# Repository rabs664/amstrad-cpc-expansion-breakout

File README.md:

# amstrad-cpc-expansion-breakout
Simple PCB with labels and header pins for the Amstrad CPC Expansion Bus, compatible with an MX4 connector.

Allows Amstrad CPC Expansion bus signals to be monitored using the labels without having to remember the pin position on the connector.

Source contains Eagle schematic, board and cam output (gerber) files.

Note there is no ESD protection and the headers connect directly to the expansion bus, so care should be taken at all times to prevent accidents.

see Wiki for more info.

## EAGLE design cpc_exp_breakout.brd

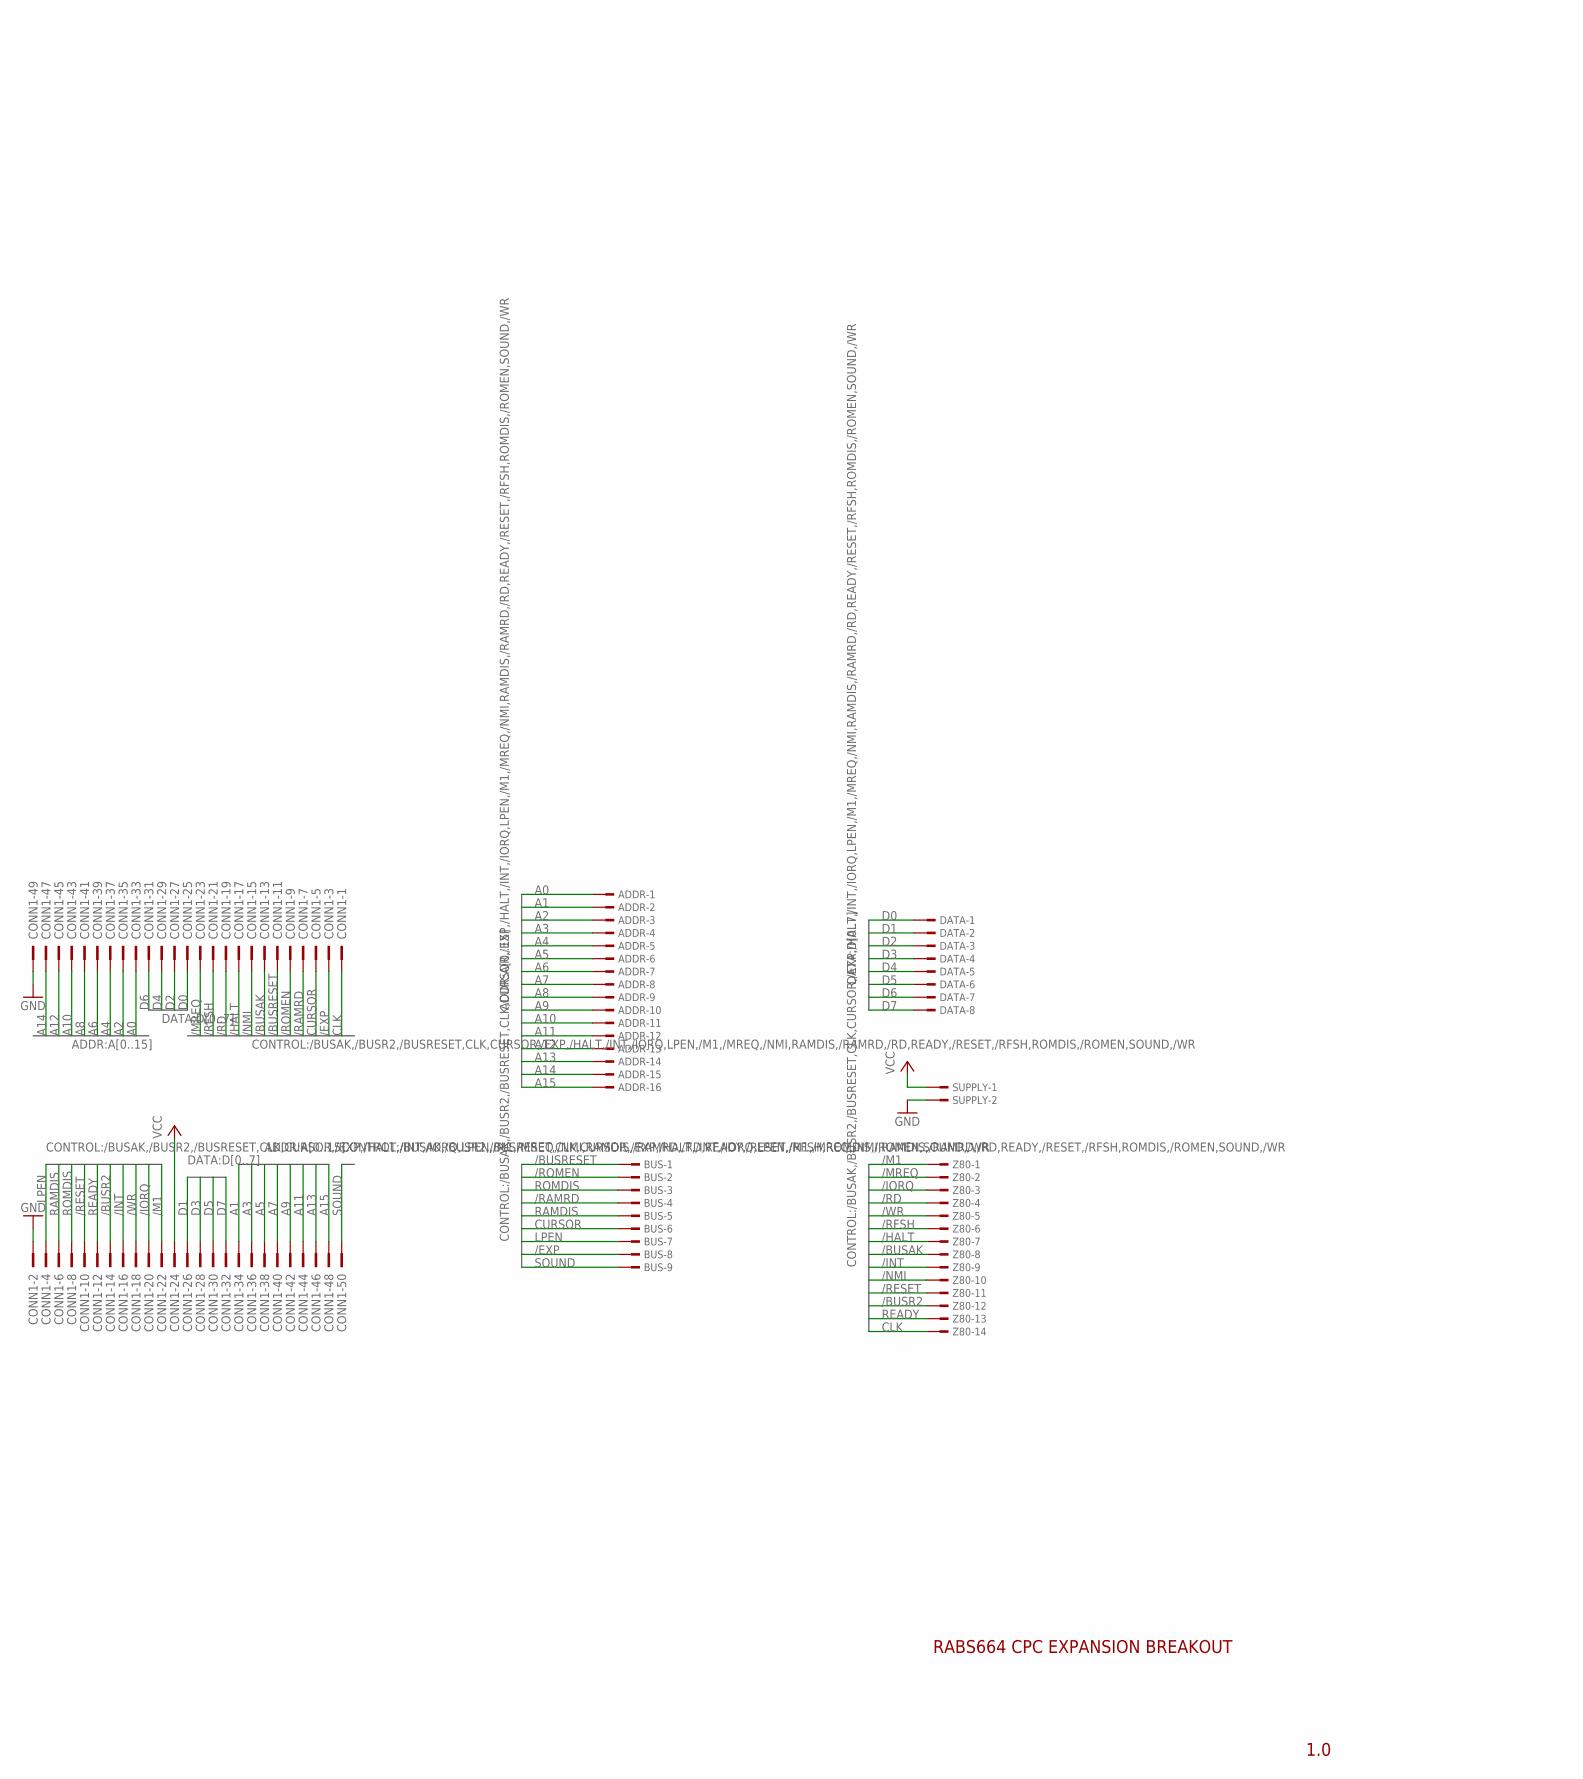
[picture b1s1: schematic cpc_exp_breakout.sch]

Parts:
ADDR: TSW-116-07-G-S; TSW-116-XX-G-S
BUS: TSW-109-07-G-S; TSW-109-XX-G-S
CONN1: 2550-; PAK100/2500-50
DATA: TSW-108-07-G-S; TSW-108-XX-G-S
SUPPLY: TSW-102-07-G-S; TSW-102-XX-G-S
Z80: TSW-114-07-G-S; TSW-114-XX-G-S

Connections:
/BUSAK: CONN1.13, Z80.8
/BUSR2: CONN1.14, Z80.12
/BUSRESET: BUS.1, CONN1.11
/EXP: BUS.8, CONN1.3
/HALT: CONN1.17, Z80.7
/INT: CONN1.16, Z80.9
/IORQ: CONN1.20, Z80.3
/M1: CONN1.22, Z80.1
/MREQ: CONN1.23, Z80.2
/NMI: CONN1.15, Z80.10
/RAMRD: BUS.4, CONN1.7
/RD: CONN1.19, Z80.4
/RESET: CONN1.10, Z80.11
/RFSH: CONN1.21, Z80.6
/ROMEN: BUS.2, CONN1.9
/WR: CONN1.18, Z80.5
A0: ADDR.1, CONN1.33
A1: ADDR.2, CONN1.34
A2: ADDR.3, CONN1.35
A3: ADDR.4, CONN1.36
A4: ADDR.5, CONN1.37
A5: ADDR.6, CONN1.38
A6: ADDR.7, CONN1.39
A7: ADDR.8, CONN1.40
A8: ADDR.9, CONN1.41
A9: ADDR.10, CONN1.42
A10: ADDR.11, CONN1.43
A11: ADDR.12, CONN1.44
A12: ADDR.13, CONN1.45
A13: ADDR.14, CONN1.46
A14: ADDR.15, CONN1.47
A15: ADDR.16, CONN1.48
CLK: CONN1.1, Z80.14
CURSOR: BUS.6, CONN1.5
D0: CONN1.25, DATA.1
D1: CONN1.26, DATA.2
D2: CONN1.27, DATA.3
D3: CONN1.28, DATA.4
D4: CONN1.29, DATA.5
D5: CONN1.30, DATA.6
D6: CONN1.31, DATA.7
D7: CONN1.32, DATA.8
GND: CONN1.2, CONN1.49, SUPPLY.2
LPEN: BUS.7, CONN1.4
RAMDIS: BUS.5, CONN1.6
READY: CONN1.12, Z80.13
ROMDIS: BUS.3, CONN1.8
SOUND: BUS.9, CONN1.50
VCC: CONN1.24, SUPPLY.1

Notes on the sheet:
1.0
RABS664 CPC EXPANSION BREAKOUT

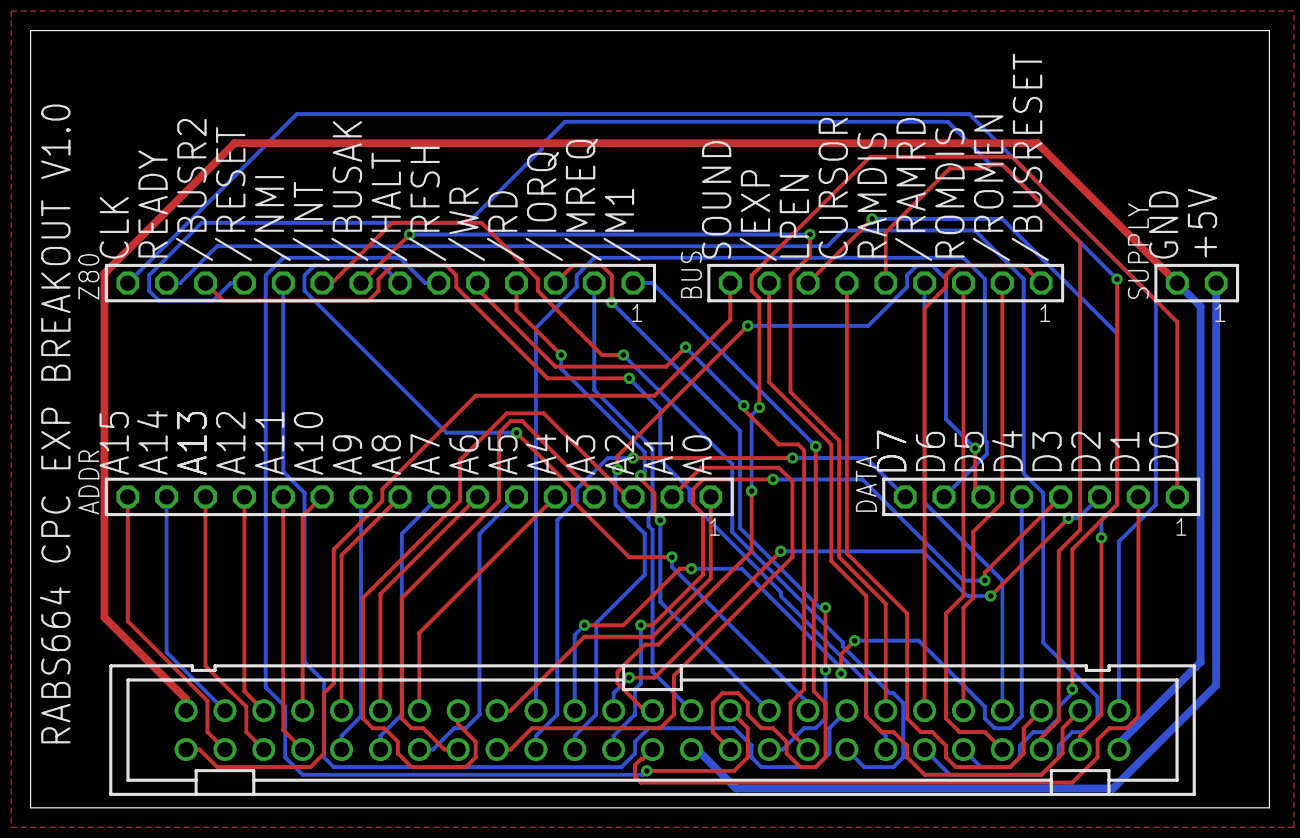
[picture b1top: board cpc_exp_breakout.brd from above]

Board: 2 copper layers, 81.0 x 50.8 mm, 6 parts (0 on the bottom side), 49 nets.

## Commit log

2023-03-25 Add files via upload
    Results of continuity check back to Amstrad CPC 6128 PCB
